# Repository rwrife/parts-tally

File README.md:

# Parts Tally

**Parts Tally is a USB-powered ESP32-C3 smart bin scale that counts small workshop parts by calibrated unit weight and serves a private local inventory app—no cloud account required.**

## Motivation

Counting screws, nuts, washers, crimp terminals, and other small repeated parts by hand is slow. Visual estimates are unreliable, while commercial inventory systems are often expensive or cloud-dependent. Parts Tally turns a removable parts bin into a local smart scale: select a saved part profile, tare the empty bin, and see an estimated count plus a low-stock state.

## Target users

- Home workshops and makerspaces
- Electronics benches with reels, connectors, and loose hardware
- Small repair shops that want a lightweight, account-free stock signal
- Hobbyists who need repeatable counts rather than purchasing automation

## Use cases

1. **Fast recount:** place a known bin on the platform, select its profile, and estimate count from net mass / calibrated unit mass.
2. **Low-stock check:** show green/amber/red locally against a user-defined threshold.
3. **Calibration:** weigh an empty bin, then a known sample (for example 20 washers) to derive unit mass.
4. **Portable records:** export profiles and count history as JSON or CSV from the local app.
5. **Manual correction:** override a noisy estimate and preserve an auditable correction without pretending the scale is exact.

## Intended workflow

1. Assemble the low-voltage load-cell platform and connect it by USB-C to a 5 V supply.
2. On first use, the device exposes a temporary local setup access point; the user configures Wi-Fi or continues in direct-device mode.
3. Open the phone-friendly local web app, create a part profile, tare the empty bin, and run a known-count calibration.
4. Place the loaded bin on the platform. The device filters readings, reports stability and uncertainty, then estimates count.
5. Review or correct the count, set a threshold, and export local data when desired.

## MVP

- ESP32-C3 controller with USB power, Wi-Fi, and BLE-capable hardware
- One TAL220B 5 kg 4-wire bar load cell and SparkFun SEN-15242/NAU7802 bridge ADC module
- Physical tare/calibrate button and RGB status indication
- Stable-weight detection, tare, multi-point known-count calibration, and count uncertainty
- On-device local API plus responsive installable PWA
- Local profile/history storage with JSON and CSV export/import
- Offline/direct-device mode after initial assets are loaded
- Reproducible firmware and app builds
- Editable KiCad schematic and custom carrier PCB after the module prototype is validated

## Non-goals

- Trade-certified weighing or legal-for-commerce measurements
- Medical, food-safety, life-safety, or unattended industrial process control
- Exact counting of mixed parts or parts whose unit mass varies substantially
- Mains wiring, battery charging in the first revision, or cloud accounts
- Automatic purchasing or supplier-stock claims

## Hardware at a glance

```text
5 V USB-C supply
       |
XIAO ESP32-C3 ---- planned status RGB LED
   |       |
   |       +------ tare/calibrate button
   |
   +-- SparkFun SEN-15242 / NAU7802 -- TAL220B 5 kg bar load cell
   |
   +-- local Wi-Fi HTTP/WebSocket API ------ phone/desktop PWA
```

Prototype target: approximately **USD $35–$55**, excluding a user-printed enclosure. This is a planning range, not a quote; current prices and availability must be re-verified before ordering.

## Safety limits

Parts Tally is a SELV/USB 5 V bench device. Do not connect it to mains, exceed the load cell's rated load, use it as a structural support, or rely on it for safety-critical stock decisions. Provide overload stops in the mechanical design. A printed enclosure must not carry loads through the PCB. This project is not a certified scale.

## Privacy, permissions, and storage

- No account, analytics, or cloud service is required.
- Profiles, calibration values, thresholds, and history are stored on the device and/or in browser-local storage as documented by the app implementation.
- Network access is limited to local device discovery/setup and the device API.
- BLE/Wi-Fi permissions are requested only when a chosen provisioning flow needs them.
- Export and import are explicit user actions; secrets are excluded from exports.
- Optional future integrations must remain opt-in and preserve a useful offline mode.

## Source-of-truth policy

Final BOM data belongs in **KiCad schematic symbol properties** (`Manufacturer`, `MPN`, supplier fields, and BOM notes) and is exported to `bom/bom.csv`. `bom/preliminary-bom.csv` is only a planning document and must not drift into a competing source of truth.

The hardware release uses real editable KiCad sources—not image-only drawings—including:

- `hardware/kicad/parts-tally.kicad_pro`
- `hardware/kicad/parts-tally.kicad_sch`
- `hardware/kicad/parts-tally.kicad_pcb`

The project, schematic, routed two-layer PCB, custom library, validation notes, OpenSCAD platform source, and schematic-exported BOM now exist under `hardware/kicad/`, `hardware/reports/`, `hardware/mechanical/`, and `bom/`. The tagged release workflow generates and validates Gerber/drill/CPL/PDF/assembly/render artifacts; generated outputs supplement rather than replace editable source. No assembled-board, fabricated-board, or physical-test claim is implied.

## Current status and milestones

1. Requirements, measurement model, and architecture risk review — baselined in the editable documents below; this is documentation/static evidence only
2. Datasheet-backed module-chain selection and synthetic capture harness — complete; physical fixture/bench characterization explicitly pending
3. Editable KiCad schematic and schematic-backed BOM — implemented; CI-native ERC and static review evidence are recorded under `hardware/reports/`
4. Firmware and local protocol with host-side tests
5. Accessible local PWA and import/export — implemented and software-tested with a mock transport; physical-device/browser verification remains pending
6. Carrier PCB, native DRC, and editable mechanical platform — implemented and statically validated; physical fit/assembly/bring-up remains pending
7. Tagged fabrication release package and unexecuted assembly/bring-up procedures — release-candidate automation implemented; physical evidence remains pending

Baseline contracts:

- [System architecture and count/uncertainty model](docs/architecture.md)
- [Reviewed measurable requirements](hardware/requirements.md)
- [Planned module wiring and carrier boundary](hardware/interfaces.md)
- [Datasheet-backed component selection](hardware/selection.md)
- [Planned module build and capture record](hardware/module-prototype.md)
- [Datasheet/source manifest](hardware/datasheets/manifest.json)
- [Unexecuted prototype verification plan](docs/verification-plan.md)
- [Assembly, calibration, and bring-up procedure](docs/assembly-and-bring-up.md)
- [Integrated release verification record](docs/release-verification.md)
- [Release packaging and fabrication assumptions](release/README.md)
- [Licensing and third-party notices](LICENSES.md)
- [Risk register](docs/risk-register.md)
- [Machine-readable architecture contract](docs/architecture-contract.json)

Run `python3 scripts/validate_contract.py` and `python3 -m unittest discover -s tests -v` to validate document, safety, dependency, risk, evidence-state, and synthetic capture-tool consistency.

See [PLAN.md](PLAN.md), [hardware/README.md](hardware/README.md), and the GitHub issue backlog.

## Development quickstart

The implementation toolchains will be pinned in the first project-skeleton issue. The intended commands are:

```bash
# Firmware (PlatformIO)
cd firmware
pio run
pio test -e native

# Companion PWA (TypeScript/Vite, Node 22.23.1 / npm 10.9.8)
cd app
npm ci
npm run lint
npm run typecheck
npm test
npm run build
npx playwright install chromium # first local run
npm run test:e2e
```

See `app/VERIFICATION.md` for the latest exact software verification record. App end-to-end tests use a mock device and do not establish physical integration.

## Contributing

Keep changes issue-scoped and evidence-backed. Never report physical bench testing unless a real assembled prototype and procedure were used; distinguish static analysis, simulation, firmware/app tests, and physical measurements.

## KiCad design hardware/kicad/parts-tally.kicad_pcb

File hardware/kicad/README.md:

# Parts Tally KiCad source

This directory contains the editable KiCad 9 schematic and routed two-layer carrier PCB for revision A0. The design is static-analysis/DRC reviewed but has not been fabricated, assembled, electrically measured, calibrated, or field tested.

## Files

- `parts-tally.kicad_pro` — KiCad project metadata and board rules.
- `parts-tally.kicad_sch` — editable schematic and BOM source of truth.
- `parts-tally.kicad_pcb` — editable 100 × 60 mm routed board source.
- `lib/parts-tally.kicad_sym` — project-local XIAO ESP32-C3 and NAU7802 symbols.
- `lib/parts-tally.pretty/XIAO_ESP32C3.kicad_mod` — project-local module footprint.
- `generate_schematic.py` — reproducible schematic generator.
- `generate_pcb.py` — reproducible board outline, placement, rules, labels, mounting holes, and antenna keepouts from the KiCad XML netlist.
- `pre_route_critical.py` — fixed VBUS/I2C/+5 V escapes around the USB locator holes and XIAO antenna keepout.
- `route_pcb.py` — netclass-aware Specctra DSN/SES exchange and idempotent GND-pour fill.
- `finish_route.py` — deterministic local TP2 branch left by the autorouter.
- `validate_hardware.py` — schematic pin map, net-label, NC, BOM-property, and extraction checks.
- `validate_pcb.py` — PCB/netlist parity, geometry, mounting, keepout, zone, route-width, and analog-pair checks.
- `export_bom.py` — deterministic export from schematic properties to `../../bom/bom.csv`.

The XIAO library source and adaptation are documented in `lib/README.md`.

## Board design summary

- 100 × 60 mm, two copper layers, four 3.2 mm M3 mounting holes.
- U1 sits at the top-right edge with four layer-specific rule areas. Copper, tracks, vias, and components are prohibited in the transformed XIAO/ESP32-C3 antenna regions.
- J1 is a **power-only** USB-C UFP. Its locator-hole geometry requires two bottom-tented 0.60/0.30 mm via-in-pad transitions to tie the duplicated VBUS pad locations on B.Cu. D+/D-/SBU remain intentionally NC.
- VBUS and protected +5 V use 0.50 mm trunks with short 0.20 mm branches/neck-downs; low-current 3.3 V distribution uses 0.20 mm routing. Thirteen 0.15 mm FreeRouting neck-down segments occur only at constrained fine-pitch pads and remain above the selected prototype process minimum.
- `/LC_S+` and `/LC_S-` measure 10.01/11.04 mm (1.04 mm delta). `/AIN+` and `/AIN-`, including filter branches, measure 37.71/30.91 mm (6.80 mm delta). These are low-bandwidth bridge signals, not timing-matched digital pairs.
- Solid-connected GND pours cover F.Cu and B.Cu; five GND vias join the planes. The bottom plane is the preferred return path.
- TP1–TP10 expose VBUS, protected +5 V, 3V3, GND, AVDD, I2C, bridge inputs, and VBG.
- J2 pin order is 1 E+, 2 E-, 3 S+, 4 S-. Verify the real harness continuity and wire colors before power.

## Validate the committed design

Use KiCad 9 and Python 3.11+:

```bash
python3 -m venv .venv
. .venv/bin/activate
pip install -r hardware/kicad/requirements.txt
python hardware/kicad/validate_hardware.py
python hardware/kicad/export_bom.py --check

kicad-cli sch erc --exit-code-violations \
  -o /tmp/parts-tally-erc.rpt hardware/kicad/parts-tally.kicad_sch
kicad-cli sch export netlist --format kicadxml \
  -o /tmp/parts-tally.xml hardware/kicad/parts-tally.kicad_sch
python hardware/kicad/validate_pcb.py \
  hardware/kicad/parts-tally.kicad_pcb --netlist /tmp/parts-tally.xml
kicad-cli pcb drc --severity-all --all-track-errors --exit-code-violations \
  -o /tmp/parts-tally-drc.rpt hardware/kicad/parts-tally.kicad_pcb
```

The GitHub workflow runs the native KiCad commands in `kicad/kicad:9.0`, avoiding host-version ambiguity. Review evidence is in `../reports/layout-validation.md` and `../reports/generated/`.

## Regenerate placement and reroute

The committed `.kicad_pcb` is the reviewed editable layout source. The placement and critical escapes are reproducible; FreeRouting is nondeterministic, so a new autoroute is a new design revision and must pass all checks and visual review.

```bash
kicad-cli sch export netlist --format kicadxml \
  -o /tmp/parts-tally.xml hardware/kicad/parts-tally.kicad_sch
python hardware/kicad/generate_pcb.py \
  --netlist /tmp/parts-tally.xml --output hardware/kicad/parts-tally.kicad_pcb
python hardware/kicad/pre_route_critical.py hardware/kicad/parts-tally.kicad_pcb
python hardware/kicad/route_pcb.py export-dsn \
  hardware/kicad/parts-tally.kicad_pcb /tmp/parts-tally.dsn
java -jar freerouting-2.3.0.jar --gui.enabled=false \
  -de /tmp/parts-tally.dsn -do /tmp/parts-tally.ses \
  -mp 30 -mt 4 -us Hybrid -hr 1:1 -is prioritized
python hardware/kicad/route_pcb.py import-ses \
  hardware/kicad/parts-tally.kicad_pcb /tmp/parts-tally.ses
python hardware/kicad/finish_route.py hardware/kicad/parts-tally.kicad_pcb
python hardware/kicad/route_pcb.py add-ground-zones \
  hardware/kicad/parts-tally.kicad_pcb
```

The recorded local route used FreeRouting 2.3.0 on Java 25 and KiCad 9.0.9. Do not accept an autorouter success code as evidence: run KiCad DRC and inspect the report.

## Sourcing and mechanics

Every populated symbol carries `Manufacturer`, `MPN`, supplier/source, supplier PN, datasheet, dated cost/stock observations, and BOM notes. `bom/bom.csv` is generated from those properties. `bom/non-schematic-items.csv` separately tracks the load cell, mating parts, printed pieces, cable restraint, feet, overload stops, and fasteners. Re-check all stock and prices before ordering.

Editable enclosure/platform source is under `../mechanical/`; force flows from top plate → load cell → base and does not pass through the PCB. Preserve the antenna no-metal/no-fastener volume when adapting the enclosure.

## Important limitations

This remains a PCB-layout/static-analysis deliverable. Native ERC/DRC and structural checks pass, while the installed KiCad MCP analyzer lacks `pcbnew` and no local EMC/SPICE analyzer scripts are available. Issue #7 adds a tagged KiCad 9 workflow that regenerates and validates the Gerber/drill/CPL archive; those generated files are not preferred editable source or proof of fabrication. There is no assembled prototype, continuity record, USB current measurement, RF/EMC measurement, load test, calibration, thermal test, or field test. The device remains USB/SELV-only and is not legal-for-trade or safety certified.

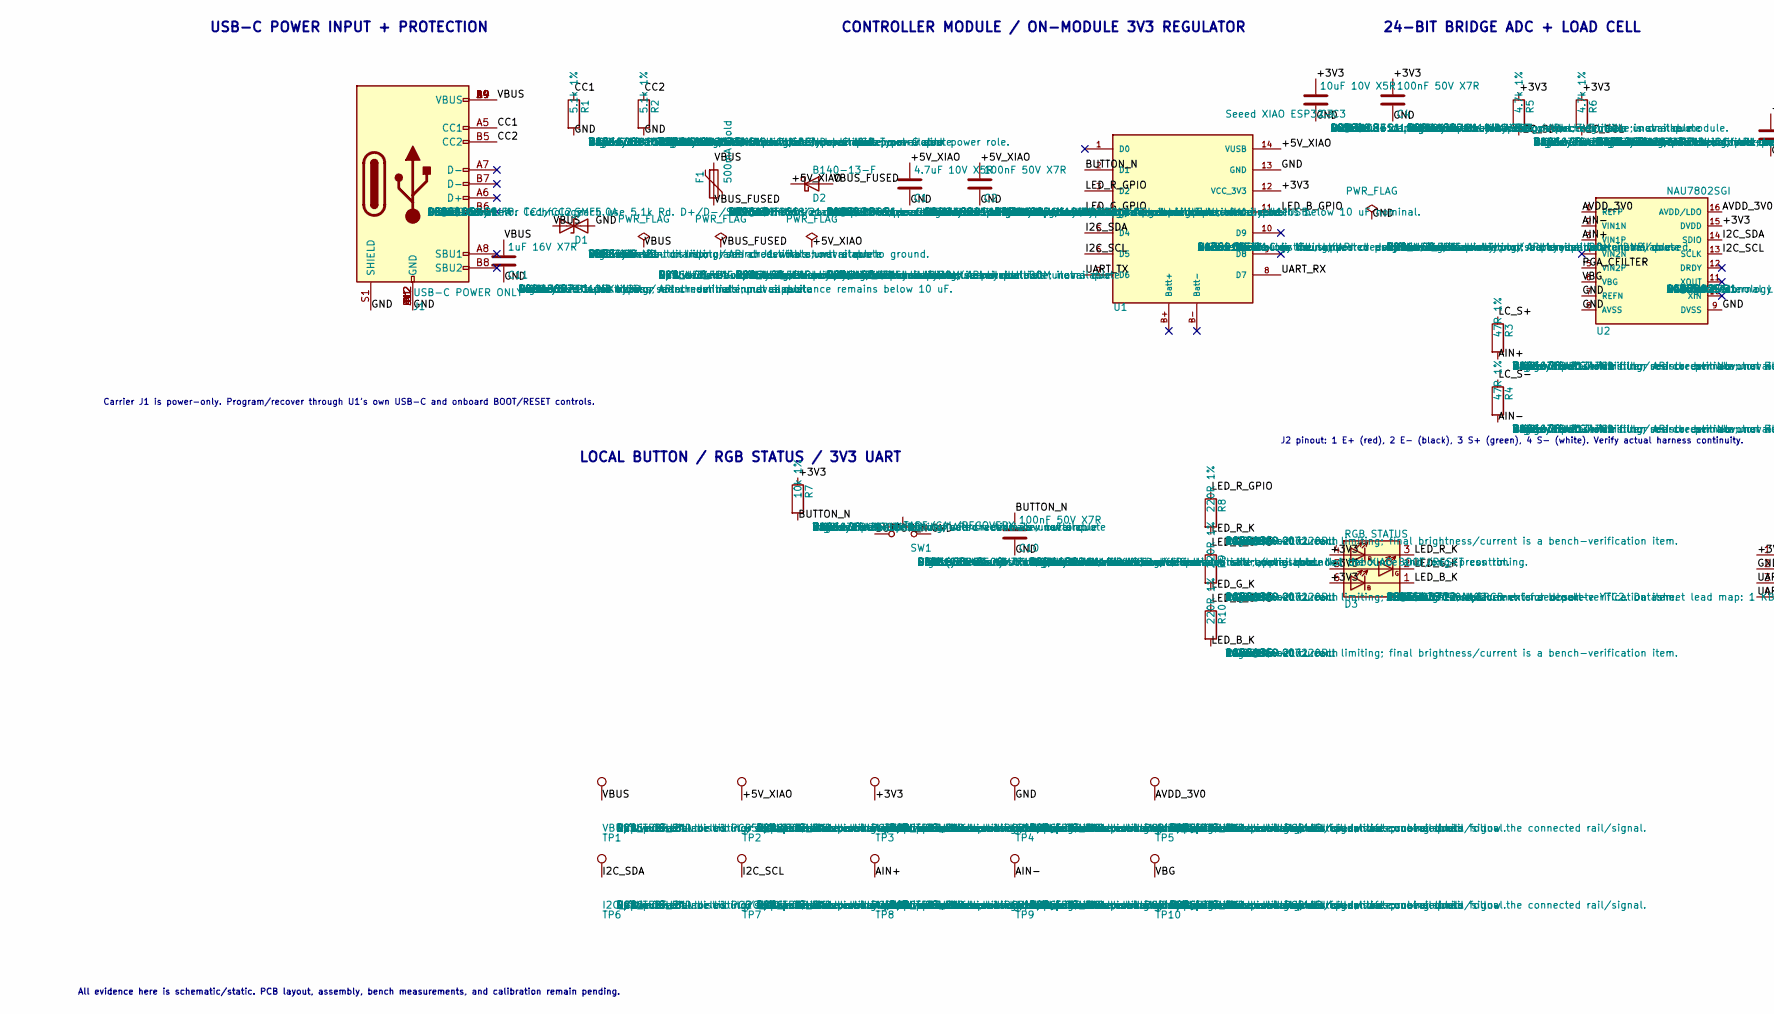
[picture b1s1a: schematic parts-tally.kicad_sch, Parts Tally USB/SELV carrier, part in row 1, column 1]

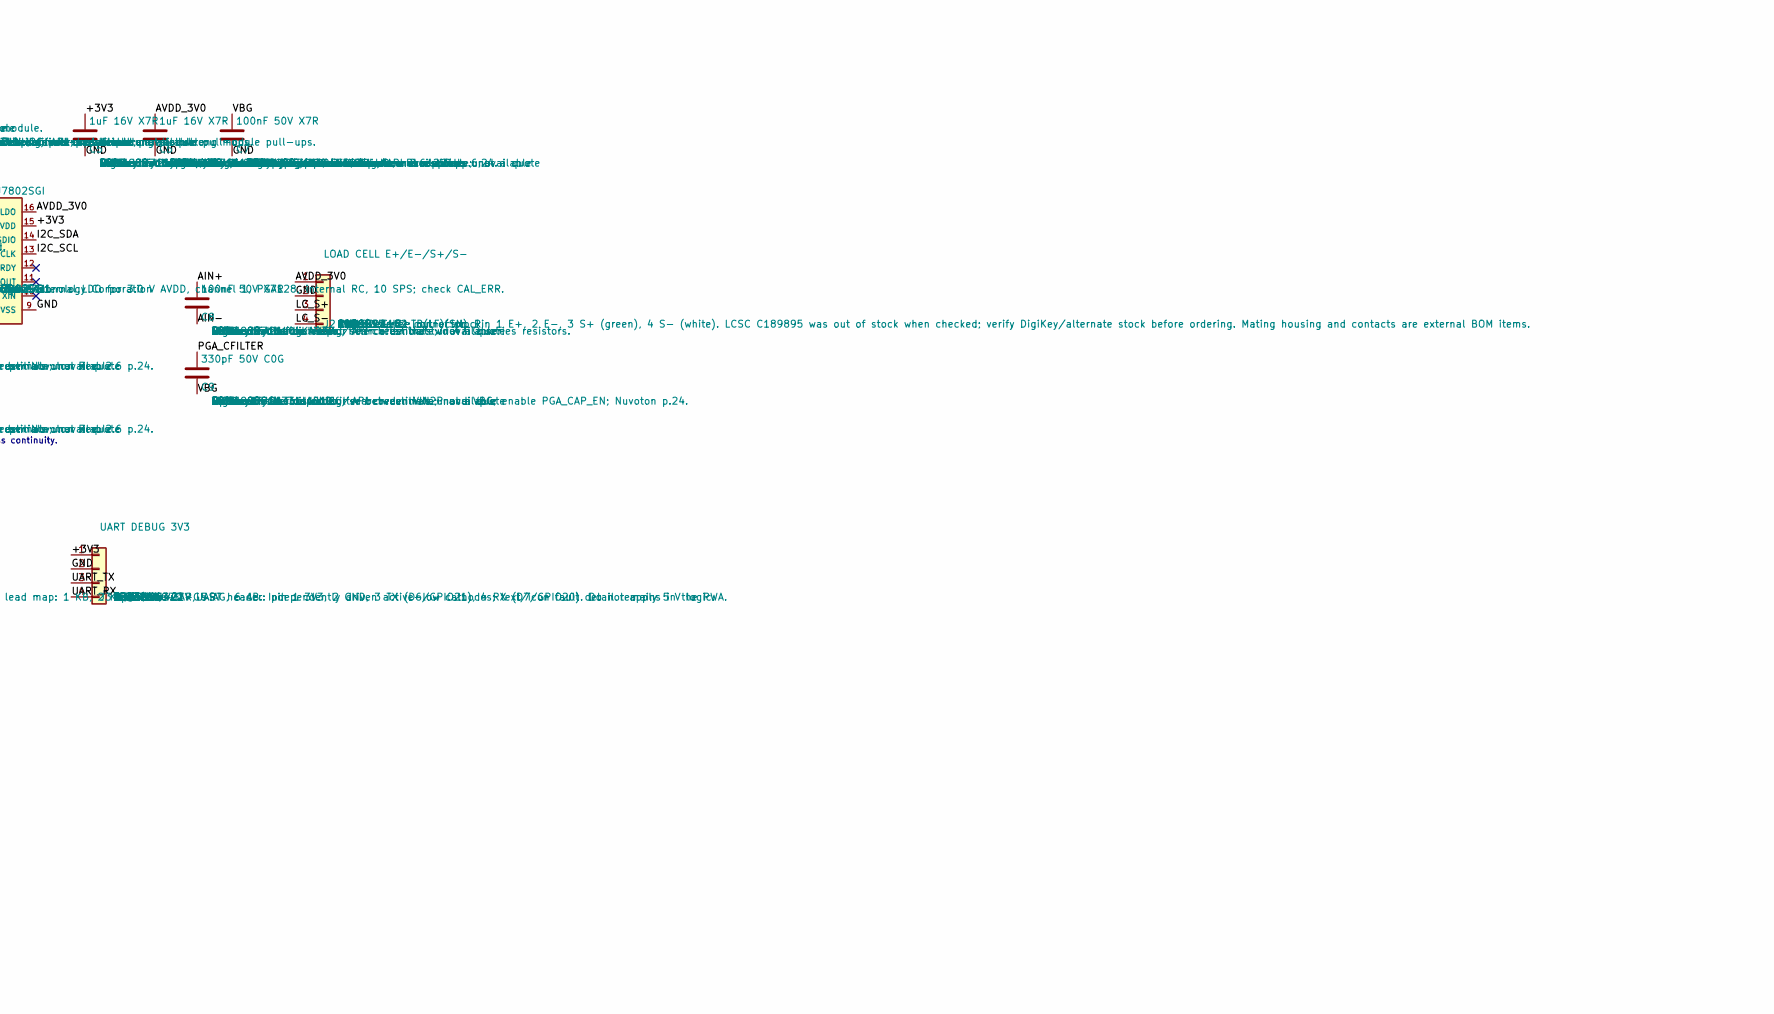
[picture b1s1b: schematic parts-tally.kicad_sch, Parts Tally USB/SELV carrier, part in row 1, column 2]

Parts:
C1: 4.7uF 10V X5R; C_1206_3216Metric; MPN GRM31CR61A475KA01L
C2, C4, C7, C8, C10: 100nF 50V X7R; C_0603_1608Metric; MPN GRM188R71H104KA93D
C3: 10uF 10V X5R; C_1206_3216Metric; MPN GRM31CR61A106KA01L
C5, C6, C11: 1uF 16V X7R; C_0603_1608Metric; MPN GRM188R71C105KA12D
C9: 330pF 50V C0G; C_0603_1608Metric; MPN GRM1885C1H331JA01D
D1: SMF5.0A; D_SOD-123F; MPN SMF5.0A
D2: B140-13-F; D_SMA; MPN B140-13-F
D3: RGB STATUS; LED_Avago_PLCC6_3x2.8mm; MPN ASMT-YTC7-0AA02
F1: 500mA hold; Fuse_1812_4532Metric; MPN MF-MSMF050-2
J1: USB-C POWER ONLY; USB_C_Receptacle_GCT_USB4105-xx-A_16P_TopMnt_Horizontal; MPN USB4105-GF-A
J2: LOAD CELL E+/E-/S+/S-; JST_GH_SM04B-GHS-TB_1x04-1MP_P1.25mm_Horizontal; MPN SM04B-GHS-TB(LF)(SN)
J3: UART DEBUG 3V3; PinHeader_1x04_P2.54mm_Vertical; MPN TSW-104-07-G-S
R1, R2: 5.1k 1%; R_0603_1608Metric; MPN RC0603FR-075K1L
R3, R4: 47R 1%; R_0603_1608Metric; MPN RC0603FR-0747RL
R5, R6: 4.7k 1%; R_0603_1608Metric; MPN RC0603FR-074K7L
R7: 10k 1%; R_0603_1608Metric; MPN RC0603FR-0710KL
R8, R9, R10: 220R 1%; R_0603_1608Metric; MPN RC0603FR-07220RL
SW1: TARE/CAL/RECOVERY; SW_SPST_PTS810; MPN PTS810SJM250SMTRLFS
TP1: VBUS; TestPoint_Pad_D1.5mm; MPN PCB_TEST_PAD
TP2: +5V_XIAO; TestPoint_Pad_D1.5mm; MPN PCB_TEST_PAD
TP3: +3V3; TestPoint_Pad_D1.5mm; MPN PCB_TEST_PAD
TP4: GND; TestPoint_Pad_D1.5mm; MPN PCB_TEST_PAD
TP5: AVDD_3V0; TestPoint_Pad_D1.5mm; MPN PCB_TEST_PAD
TP6: I2C_SDA; TestPoint_Pad_D1.5mm; MPN PCB_TEST_PAD
TP7: I2C_SCL; TestPoint_Pad_D1.5mm; MPN PCB_TEST_PAD
TP8: AIN+; TestPoint_Pad_D1.5mm; MPN PCB_TEST_PAD
TP9: AIN-; TestPoint_Pad_D1.5mm; MPN PCB_TEST_PAD
TP10: VBG; TestPoint_Pad_D1.5mm; MPN PCB_TEST_PAD
U1: Seeed XIAO ESP32-C3; XIAO_ESP32C3; MPN 113991054
U2: NAU7802SGI; SOIC-16_3.9x9.9mm_P1.27mm; MPN NAU7802SGI

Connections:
/+3V3: C3.1, C4.1, C5.1, D3.4 (AR), D3.5 (AG), D3.6 (AB), J3.1, R5.1, R6.1, R7.1, TP3.1, U1.12 (VCC_3V3), U2.15 (DVDD)
/+5V_XIAO: C1.1, C2.1, D2.1 (K), TP2.1, U1.14 (VUSB)
/AIN+: C8.1, R3.2, TP8.1, U2.3 (VIN1P)
/AIN-: C8.2, R4.2, TP9.1, U2.2 (VIN1N)
/AVDD_3V0: C6.1, J2.1, TP5.1, U2.1 (REFP), U2.16 (AVDD/LDO)
/BUTTON_N: C10.1, R7.2, SW1.1, U1.2 (D1)
/CC1: J1.A5 (CC1), R1.1
/CC2: J1.B5 (CC2), R2.1
/GND: C1.2, C2.2, C3.2, C4.2, C5.2, C6.2, C7.2, C10.2, C11.2, D1.2 (A2), J1.A1 (GND), J1.A12 (GND), J1.B1 (GND), J1.B12 (GND), J1.S1 (SHIELD), J2.2, J3.2, R1.2, R2.2, SW1.2, TP4.1, U1.13 (GND), U2.7 (REFN), U2.8 (AVSS), U2.9 (DVSS)
/I2C_SCL: R6.2, TP7.1, U1.6 (D5), U2.13 (SCLK)
/I2C_SDA: R5.2, TP6.1, U1.5 (D4), U2.14 (SDIO)
/LC_S+: J2.3, R3.1
/LC_S-: J2.4, R4.1
/LED_B_GPIO: R10.1, U1.11 (D10)
/LED_B_K: D3.1 (KB), R10.2
/LED_G_GPIO: R9.1, U1.4 (D3)
/LED_G_K: D3.2 (KG), R9.2
/LED_R_GPIO: R8.1, U1.3 (D2)
/LED_R_K: D3.3 (KR), R8.2
/PGA_CFILTER: C9.1, U2.5 (VIN2P)
/UART_RX: J3.4, U1.8 (D7)
/UART_TX: J3.3, U1.7 (D6)
/VBG: C7.1, C9.2, TP10.1, U2.6 (VBG)
/VBUS: C11.1, D1.1 (A1), F1.1, J1.A4 (VBUS), J1.A9 (VBUS), J1.B4 (VBUS), J1.B9 (VBUS), TP1.1
/VBUS_FUSED: D2.2 (A), F1.2

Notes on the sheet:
USB-C POWER INPUT + PROTECTION
CONTROLLER MODULE / ON-MODULE 3V3 REGULATOR
24-BIT BRIDGE ADC + LOAD CELL
LOCAL BUTTON / RGB STATUS / 3V3 UART
Carrier J1 is power-only. Program/recover through U1's own USB-C and onboard BOOT/RESET controls.
J2 pinout: 1 E+ (red), 2 E- (black), 3 S+ (green), 4 S- (white). Verify actual harness continuity.
All evidence here is schematic/static. PCB layout, assembly, bench measurements, and calibration remain pending.

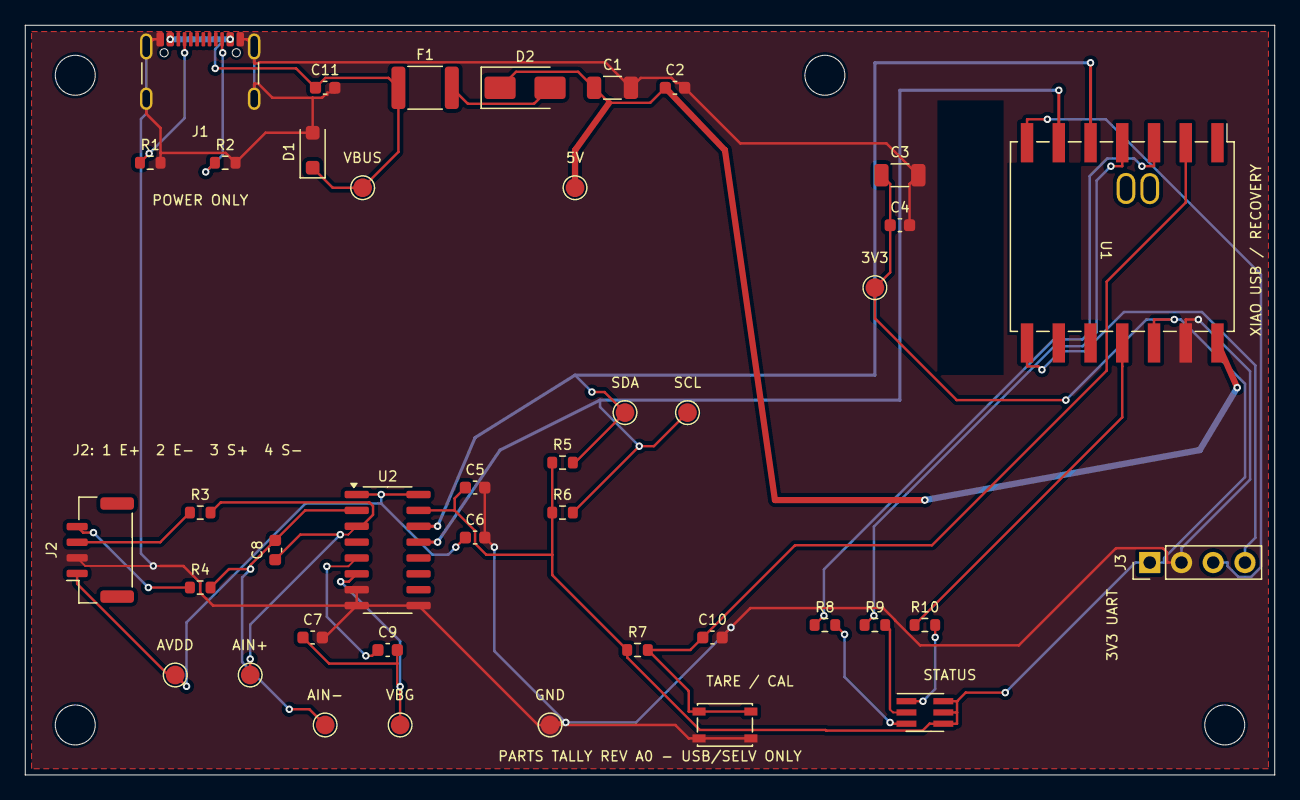
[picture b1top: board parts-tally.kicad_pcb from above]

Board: 2 copper layers, 100.0 x 60.0 mm, 45 parts (0 on the bottom side), 25 nets.

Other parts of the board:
H1, H2, H3, H4: M3 PCB MOUNT - NOT IN SCALE FORCE PATH; MountingHole_3.2mm_M3

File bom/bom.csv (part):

Reference,Qty,Value,Footprint,Manufacturer,MPN,Supplier,Supplier PN,Estimated Unit Cost USD,Extended Cost USD,Price Observed UTC,Stock Observed,Cost Basis,Datasheet,BOM Comments
C1,1,4.7uF 10V X5R,Capacitor_SMD:C_1206_3216Metric,Murata,GRM31CR61A475KA01L,DigiKey,490-3902-1-ND,0.20,0.2000,2026-08-21,Not verified — distributor API credentials unavailable,Public distributor listing/search estimate; not a quote,https://www.murata.com/en-global/products/capacitor/mlcc/ove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,Protected 5 V bulk capacitor; total carrier input capacitance remains below 10 uF nominal.
"C2,C4,C10",3,100nF 50V X7R,Capacitor_SMD:C_0603_1608Metric,Murata,GRM188R71H104KA93D,DigiKey,490-1519-1-ND,0.02,0.0600,2026-08-21,Not verified — distributor API credentials unavailable,Public distributor listing/search estimate; not a quote,https://search.murata.co.jp/Ceramy/image/img/A01X/G101/ENG/G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,High-frequency bypass on protected 5 V rail. | High-frequency bypass on the 3V3 rail. | Button hardware debounce; firmware still applies bounded debounce and long-press timing.
C3,1,10uF 10V X5R,Capacitor_SMD:C_1206_3216Metric,Murata,GRM31CR61A106KA01L,LCSC,C97949,0.3351,0.3351,2026-08-21,22,1 @ $0.3351,https://search.murata.co.jp/Ceramy/image/img/A01X/G101/ENG/G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,Local bulk capacitor on the XIAO 3V3 output; regulator is on the module.
"C5,C6",2,1uF 16V X7R,Capacitor_SMD:C_0603_1608Metric,Murata,GRM188R71C105KA12D,DigiKey,TBD—verify before order,0.08,0.1600,2026-08-21,Not verified — distributor API credentials unavailable,Public distributor listing/search estimate; not a quote,https://www.murata.com/en-global/products/capacitor/mlcc/ove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,"DVDD local bypass; Nuvoton Rev. 2.6 p.24. | AVDD/LDO local bypass; low-ESR, Nuvoton Rev. 2.6 pp.6,24."
"C7,C8",2,100nF 50V X7R,Capacitor_SMD:C_0603_1608Metric,Murata,GRM188R71H104KA93D,DigiKey,TBD—verify before order,0.02,0.0400,2026-08-21,Not verified — distributor API credentials unavailable,Public distributor listing/search estimate; not a quote,https://www.murata.com/en-global/products/capacitor/mlcc/ove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,VBG bypass per Nuvoton Rev. 2.6 p.24. | Differential bridge-input filter after the two 47 Ω series resistors.
C9,1,330pF 50V C0G,Capacitor_SMD:C_0603_1608Metric,Murata,GRM1885C1H331JA01D,DigiKey,TBD—verify before order,0.05,0.0500,2026-08-21,Not verified — distributor API credentials unavailable,Public distributor listing/search estimate; not a quote,https://www.murata.com/en-global/products/capacitor/mlcc/ove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,Optional PGA-output Cfilter between VIN2P and VBG; enable PGA_CAP_EN; Nuvoton p.24.
C11,1,1uF 16V X7R,Capacitor_SMD:C_0603_1608Metric,Murata,GRM188R71C105KA12D,DigiKey,490-3897-1-ND,0.08,0.0800,2026-08-21,Not verified — distributor API credentials unavailable,Public distributor listing/search estimate; not a quote,https://www.murata.com/en-global/products/capacitor/mlcc/ove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,Local VBUS input bypass; total nominal input capacitance remains below 10 uF.
D1,1,SMF5.0A,Diode_SMD:D_SOD-123F,Littelfuse,SMF5.0A,DigiKey,F8583CT-ND,0.30,0.3000,2026-08-21,Not verified — distributor API credentials unavailable,Public distributor listing/search estimate; not a quote,https://www.littelfuse.com/assetdocs/tvs-diodes-smf-datashee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,VBUS transient clamp; place at J1 with short return to ground.
D2,1,B140-13-F,Diode_SMD:D_SMA,Diodes Incorporated,B140-13-F,LCSC,C15759,0.0856,0.0856,2026-08-21,59660,5 @ $0.0856 each,https://www.diodes.com/assets/Datasheets/ds13002.pdf,Series reverse-current block prevents carrier USB input from being back-fed by U1 USB.
D3,1,RGB STATUS,LED_SMD:LED_Avago_PLCC6_3x2.8mm,Broadcom Limited,ASMT-YTC7-0AA02,JLCPCB,C5555828,1.7772,1.7772,2026-08-22,79,1 @ $1.7772; JLCPCB extended part,https://docs.broadcom.com/docs/AV02-3819EN,"Current YTC7 replacement for obsolete YTC2. Datasheet lead map: 1 KB, 2 KG, 3 KR, 4 AR, 5 AG, 6 AB. Independently driven active-low cathodes; text/icon fault detail remains in the PWA."
F1,1,500mA hold,Fuse:Fuse_1812_4532Metric,Bourns,MF-MSMF050-2,LCSC,C17313,0.0668,0.0668,2026-08-21,47400,10 @ $0.0668 each,https://www.bourns.com/docs/product-datasheets/mf-msmf.pdf,500 mA hold / 1 A trip PPTC; preserves <500 mA normal-current design target.
J1,1,USB-C POWER ONLY,Connector_USB:USB_C_Receptacle_GCT_USB4105-xx-A_16P_TopMnt_Horizontal,Global Connector Technology,USB4105-GF-A,LCSC,C3020560,1.0659,1.0659,2026-08-21,926,1 @ $1.0659,https://gct.co/files/drawings/usb4105.pdf,Power-only UFP. CC1/CC2 each use 5.1k Rd. D+/D-/SBU are intentionally NC. Shell to GND.
J2,1,LOAD CELL E+/E-/S+/S-,Connector_JST:JST_GH_SM04B-GHS-TB_1x04-1MP_P1.25mm_Horizontal,JST,SM04B-GHS-TB(LF)(SN),LCSC,C189895,1.1182,1.1182,2026-08-21,0,1 @ $1.1182; out of stock,https://www.jst-mfg.com/product/pdf/eng/eGH.pdf,"Keyed carrier connector. Pin 1 E+, 2 E-, 3 S+ (green), 4 S- (white). LCSC C189895 was out of stock when checked; verify DigiKey/alternate stock before ordering. Mating housing and contacts are external BOM items."
J3,1,UART DEBUG 3V3,Connector_PinHeader_2.54mm:PinHeader_1x04_P2.54mm_Vertical,Samtec,TSW-104-07-G-S,JLCPCB,C3335156,0.6472,0.6472,2026-08-21,337,1 @ $0.6472,https://suddendocs.samtec.com/prints/tsw-1xx-xx-xxx-x-xx-xx-mkt.pdf,"Optional 3.3 V UART header: pin 1 3V3, 2 GND, 3 TX (D6/GPIO21), 4 RX (D7/GPIO20). Do not apply 5 V logic."
"R1,R2",2,5.1k 1%,Resistor_SMD:R_0603_1608Metric,Yageo,RC0603FR-075K1L,DigiKey,311-5.10KHRCT-ND,0.02,0.0400,2026-08-21,Not verified — distributor API credentials unavailable,Public distributor listing/search estimate; not a quote,https://www.yageo.com/upload/media/product/productsearch/dat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,USB-C CC1 Rd; 5.1 kΩ to GND per USB Type-C sink power role. | USB-C CC2 Rd; 5.1 kΩ to GND per USB Type-C sink power role.
"R3,R4",2,47R 1%,Resistor_SMD:R_0603_1608Metric,Yageo,RC0603FR-0747RL,DigiKey,311-47.0HRCT-ND,0.02,0.0400,2026-08-21,Not verified — distributor API credentials unavailable,Public distributor listing/search estimate; not a quote,https://www.yageo.com/upload/media/product/productsearch/dat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,Bridge input series filter resistor per Nuvoton Rev. 2.6 p.24.
"R5,R6",2,4.7k 1%,Resistor_SMD:R_0603_1608Metric,Yageo,RC0603FR-074K7L,DigiKey,311-4.70KHRCT-ND,0.02,0.0400,2026-08-21,Not verified — distributor API credentials unavailable,Public distributor listing/search estimate; not a quote,https://www.yageo.com/upload/media/product/productsearch/dat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,Carrier-owned 3.3 V I2C pull-up; do not parallel strong module pull-ups.
R7,1,10k 1%,Resistor_SMD:R_0603_1608Metric,Yageo,RC0603FR-0710KL,DigiKey,311-10.0KHRCT-ND,0.02,0.0200,2026-08-21,Not verified — distributor API credentials unavailable,Public distributor listing/search estimate; not a quote,https://www.yageo.com/upload/media/product/productsearch/dat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,External pull-up for dedicated active-low button.
"R8,R9,R10",3,220R 1%,Resistor_SMD:R_0603_1608Metric,Yageo,RC0603FR-07220RL,LCSC,C107696,0.0061,0.0183,2026-08-21,417400,100 @ $0.0061 each,https://www.yageo.com/upload/media/product/productsearch/dat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,RGB channel current limiting; final brightness/current is a bench-verification item.
SW1,1,TARE/CAL/RECOVERY,Button_Switch_SMD:SW_SPST_PTS810,C&K (Littelfuse),PTS810SJM250SMTRLFS,DigiKey,CKN10502CT-ND,0.20,0.2000,2026-08-21,Not verified — distributor API credentials unavailable,Public distributor listing/search estimate; not a quote,https://www.ckswitches.com/media/1476/pts810.pdf,"Dedicated user button, active low; firmware differentiates short/long hold. Not the XIAO BOOT/RESET control."
U1,1,Seeed XIAO ESP32-C3,parts-tally:XIAO_ESP32C3,"Seeed Technology Co., Ltd.",113991054,Seeed Studio,113991054,4.99,4.9900,2026-08-21,Not verified — distributor API credentials unavailable,Public distributor listing/search estimate; not a quote,https://files.seeedstudio.com/Bazaar/product_pdf/113991054.pdf,Module USB-C is the supported programming/recovery port; battery pads are DNP/unused.
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
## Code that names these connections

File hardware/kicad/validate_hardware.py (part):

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        ("J3", "3"): "UART_TX", ("J3", "4"): "UART_RX",
        ("D3", "1"): "LED_B_K", ("D3", "2"): "LED_G_K", ("D3", "3"): "LED_R_K",
        ("D3", "4"): "+3V3", ("D3", "5"): "+3V3", ("D3", "6"): "+3V3",
        ("R8", "1"): "LED_R_GPIO", ("R8", "2"): "LED_R_K",
        ("R9", "1"): "LED_G_GPIO", ("R9", "2"): "LED_G_K",
        ("R10", "1"): "LED_B_GPIO", ("R10", "2"): "LED_B_K",
    }
    for (reference, pin), expected_net in expected_connections.items():
        point = pin_point(components[reference], symbol_defs[reference], pin)
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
